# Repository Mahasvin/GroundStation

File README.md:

# GroundStation
Hardware of Ground Station for UTS Rocketry

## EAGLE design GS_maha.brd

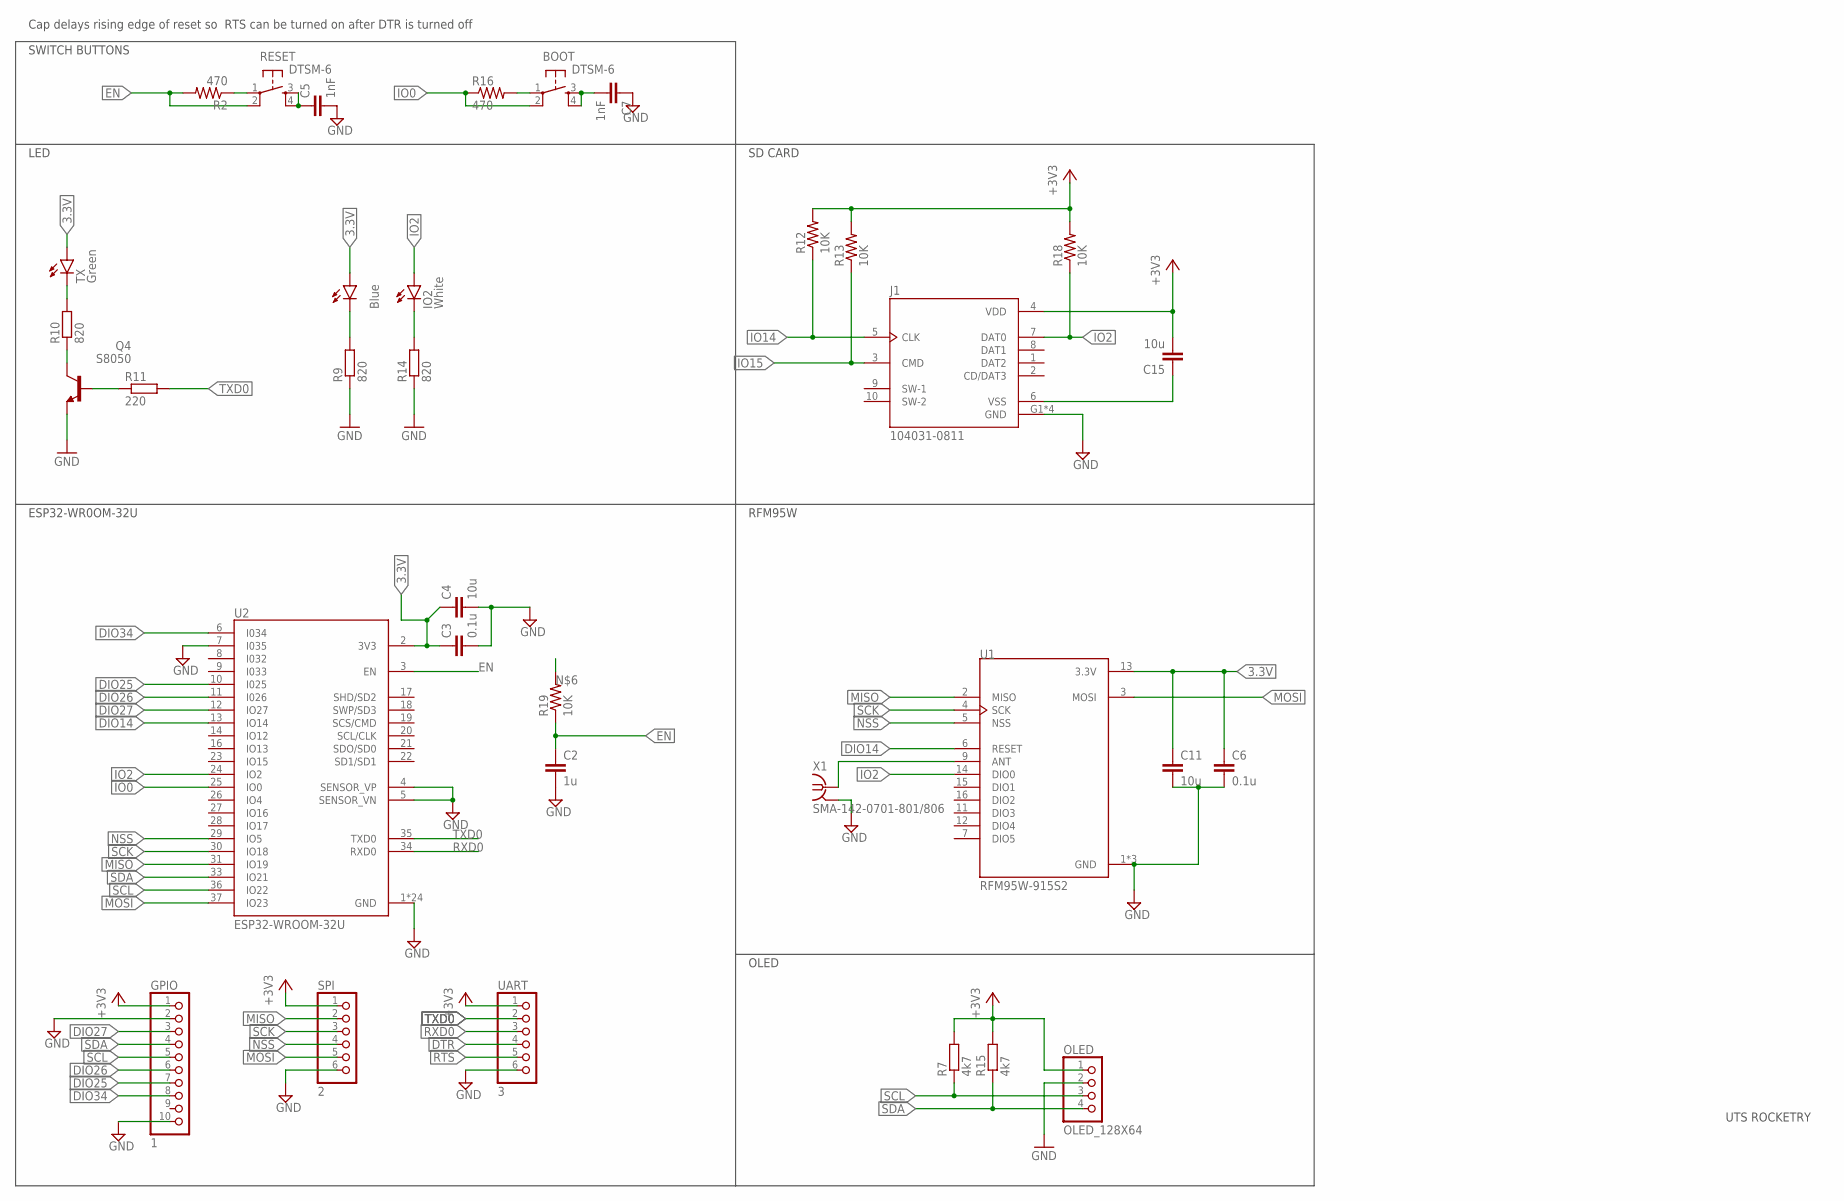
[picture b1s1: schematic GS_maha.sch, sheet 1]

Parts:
BOOT: DTSM-6
C2: 1u; C0805
C3, C6: 0.1u; C0805
C4, C11, C15: 10u; C0805
C5, C7: 1nF; C0805
GPIO: 1; 1X10
IO2: White; CHIP-LED0805
J1: 104031-0811; MOLEX_104031-0811
OLED: OLED_128X64
PWR: Blue; CHIP-LED0805
Q4: S8050; SOT95P237X110-3N
R2, R16: 470; R0805
R7, R15: 4k7; R0805
R9, R10, R14: 820; R0805
R11: 220; R0805
R12, R13, R18, R19: 10K; R0805
RESET: DTSM-6
SPI: 2; 1X06
TX: Green; CHIP-LED0805
U1: RFM95W-915S2; XCVR_RFM95W-915S2
U2: ESP32-WROOM-32U; XCVR_ESP32-WROOM-32U
UART: 3; 1X06
X1: SMA-142-0701-801/806; J502-ND-142-0701-801/806

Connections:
3.3V: C3.1, C4.1, C6.1, C11.1, PWR.A, TX.A, U1.13 (3.3V), U2.2 (3V3); also elsewhere on the board
+3V3: C15.2, GPIO.1, J1.4 (VDD), OLED.1, R7.2, R12.2, R13.2, R15.2, R18.2, SPI.1, UART.1
DIO14: U1.6 (RESET), U2.13 (IO14)
DIO25: GPIO.7, U2.10 (I025)
DIO26: GPIO.6, U2.11 (I026)
DIO27: GPIO.3, U2.12 (IO27)
DIO34: GPIO.8, U2.6 (I034)
DTR: UART.4; also elsewhere on the board
EN: C2.1, R2.2, R19.1, RESET.2, U2.3 (EN); also elsewhere on the board
GND: C2.2, C3.2, C4.2, C5.2, C6.2, C7.1, C11.2, GPIO.2, GPIO.10, J1.G1 (GND), J1.G2 (GND), J1.G3 (GND), J1.G4 (GND), OLED.2, Q4.2 (E), R9.1, R14.1, SPI.6, U1.1 (GND), U1.8 (GND), U1.10 (GND), U2.1 (GND), U2.4 (SENSOR_VP), U2.5 (SENSOR_VN), U2.7 (I035), U2.15 (GND), U2.38 (GND), U2.G.1 (GND), U2.G.2 (GND), U2.G.4 (GND), U2.G.5 (GND), U2.G.6 (GND), U2.G.7 (GND), U2.G.8 (GND), U2.G.9 (GND), U2.G.10 (GND), U2.G.11 (GND), U2.G.12 (GND), U2.G.13 (GND), U2.G.14 (GND), U2.G.15 (GND), U2.G.16 (GND), U2.G.17 (GND), U2.G.18 (GND), U2.G.19 (GND), U2.G.20 (GND), U2.G.21 (GND), U2.G.22 (GND), UART.6, X1.G@1 (2), X1.G@2 (2), X1.G@3 (2), X1.G@4 (2); also elsewhere on the board
IO0: BOOT.2, R16.1, U2.25 (IO0); also elsewhere on the board
IO2: IO2.A, J1.7 (DAT0), R18.1, U1.14 (DIO0), U2.24 (IO2)
IO14: J1.5 (CLK), R12.1
IO15: J1.3 (CMD), R13.1
MISO: SPI.2, U1.2 (MISO), U2.31 (IO19)
MOSI: SPI.5, U1.3 (MOSI), U2.37 (IO23)
unnamed: C15.1, J1.6 (VSS)
unnamed: U1.9 (ANT), X1.1
unnamed: R2.1, RESET.1
unnamed: BOOT.3, BOOT.4, C7.2
unnamed: PWR.C, R9.2
unnamed: IO2.C, R14.2
unnamed: C5.1, RESET.3, RESET.4
unnamed: BOOT.1, R16.2
unnamed: Q4.3 (C), R10.1
unnamed: Q4.1 (B), R11.1
unnamed: R10.2, TX.C
NSS: SPI.4, U1.5 (NSS), U2.29 (IO5)
RTS: UART.5; also elsewhere on the board
RXD0: U2.34 (RXD0), UART.3; also elsewhere on the board
SCK: SPI.3, U1.4 (SCK), U2.30 (IO18)
SCL: GPIO.5, OLED.3, R7.1, U2.36 (IO22)
SDA: GPIO.4, OLED.4, R15.1, U2.33 (IO21)
TXD0: R11.2, U2.35 (TXD0), UART.2; also elsewhere on the board

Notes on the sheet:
ESP32-WR0OM-32U
SWITCH BUTTONS
UTS ROCKETRY
RFM95W
LED
Cap delays rising edge of reset so RTS can be turned on after DTR is turned off
OLED
SD CARD

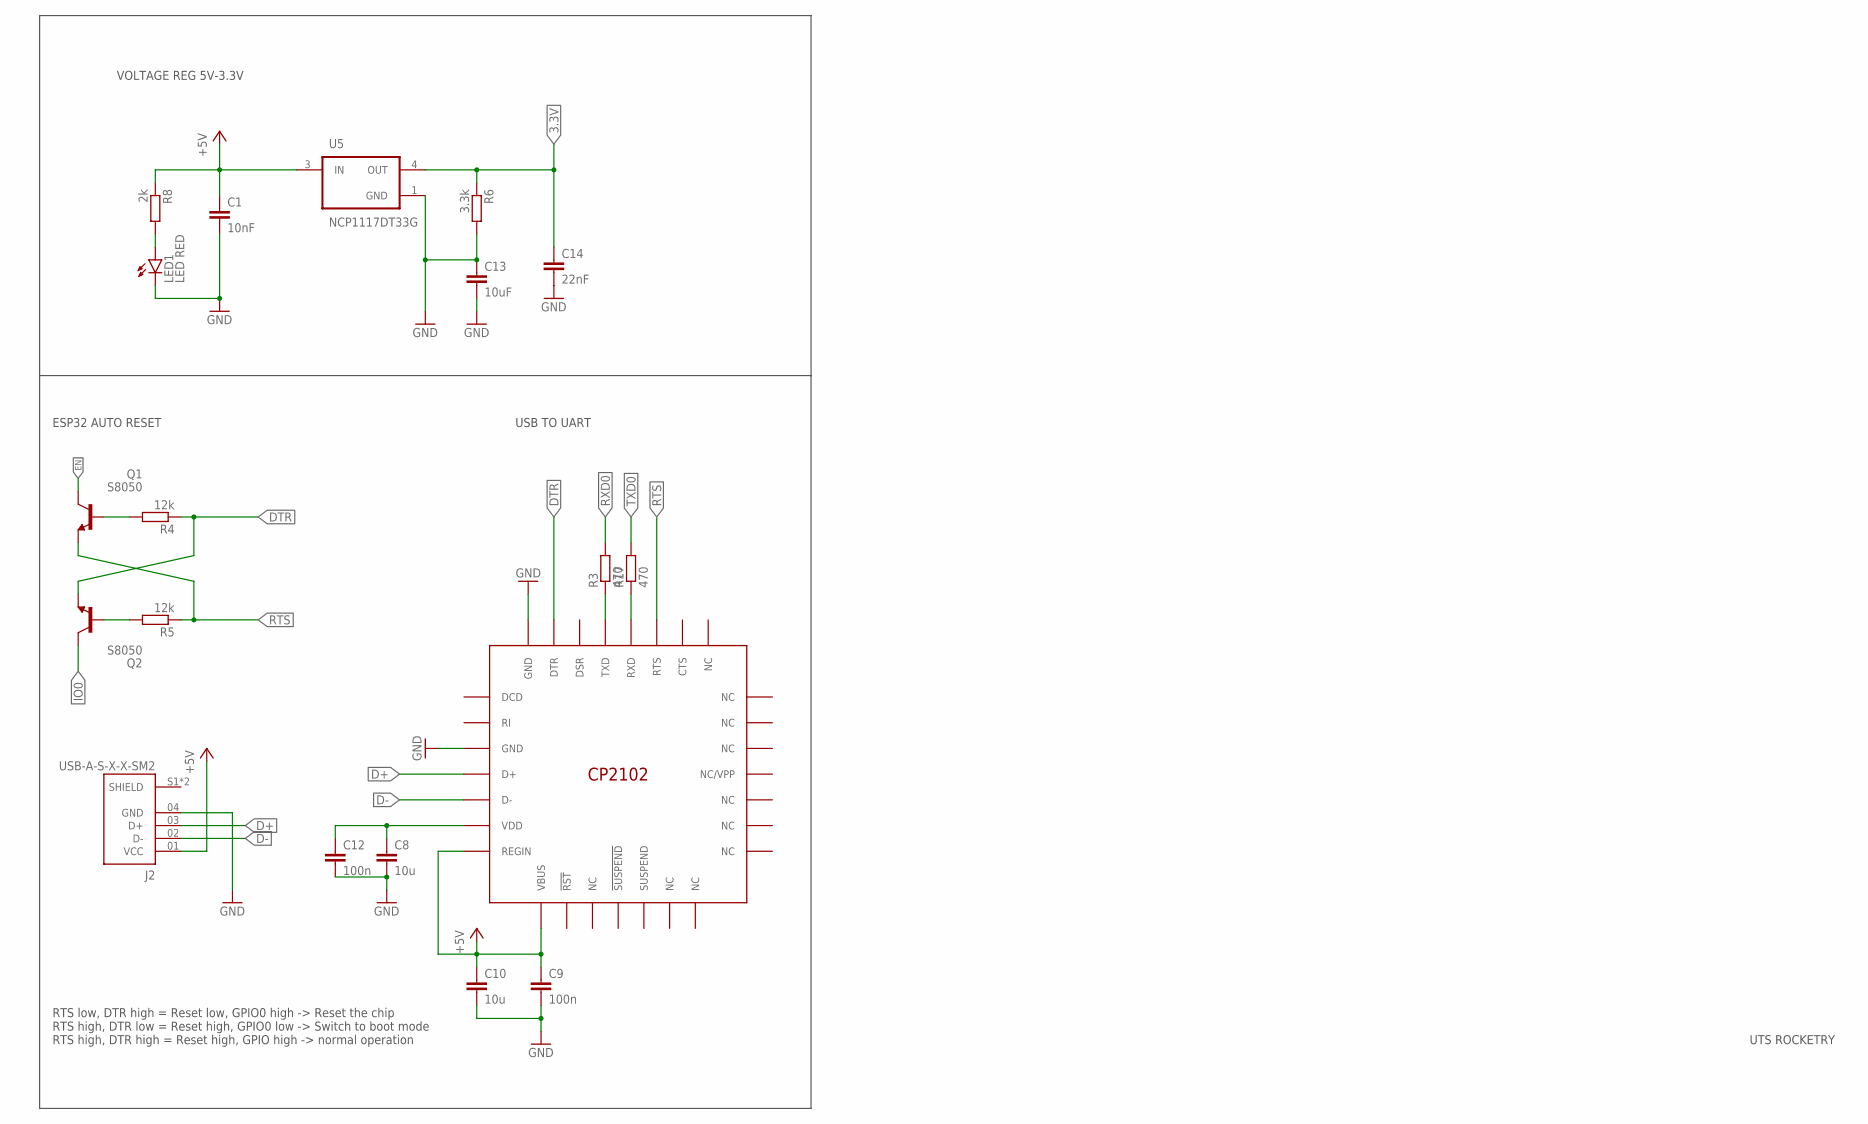
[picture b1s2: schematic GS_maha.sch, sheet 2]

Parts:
C1: 10nF; C0805
C8, C10: 10u; C0805
C9, C12: 100n; C0805
C13: 10uF; C0805
C14: 22nF; C0805
J2: USB-A-S-X-X-SM2; SAMTEC_USB-A-S-X-X-SM2
LED1: LED RED; CHIPLED_0805
Q1, Q2: S8050; SOT95P237X110-3N
R3, R17: 470; R0805
R4, R5: 12k; R0805
R6: 3.3k; R0805
R8: 2k; R0805
U3: CP2102; QFN50P500X500X100-29T300N
U5: NCP1117DT33G; VREG_NCP1117DT33G

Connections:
3.3V: C14.1, R6.1, U5.4 (OUT); also elsewhere on the board
+5V: C1.1, C9.1, C10.1, J2.01 (VCC), R8.1, U3.7 (REGIN), U3.8 (VBUS), U5.3 (IN)
D+: J2.03 (D+), U3.4 (D+)
D-: J2.02 (D-), U3.5 (D-)
DTR: Q2.2 (E), R4.1, U3.28 (DTR); also elsewhere on the board
EN: Q1.3 (C); also elsewhere on the board
GND: C1.2, C8.2, C9.2, C10.2, C12.2, C13.1, C13.2, C14.2, J2.04 (GND), LED1.C, R6.2, U3.3 (GND), U3.29 (GND), U5.1 (GND); also elsewhere on the board
IO0: Q2.3 (C); also elsewhere on the board
unnamed: R17.1, U3.25 (RXD)
unnamed: R3.1, U3.26 (TXD)
unnamed: Q1.1 (B), R4.2
unnamed: Q2.1 (B), R5.2
unnamed: C8.1, C12.1, U3.6 (VDD)
unnamed: LED1.A, R8.2
RTS: Q1.2 (E), R5.1, U3.24 (RTS); also elsewhere on the board
RXD0: R3.2; also elsewhere on the board
TXD0: R17.2; also elsewhere on the board

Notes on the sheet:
USB TO UART
ESP32 AUTO RESET
UTS ROCKETRY
RTS low, DTR high = Reset low, GPIO0 high -> Reset the chip RTS high, DTR low = Reset high, GPIO0 low -> Switch to boot mode RTS high, DTR high = Reset high, GPIO high -> normal operation
VOLTAGE REG 5V-3.3V

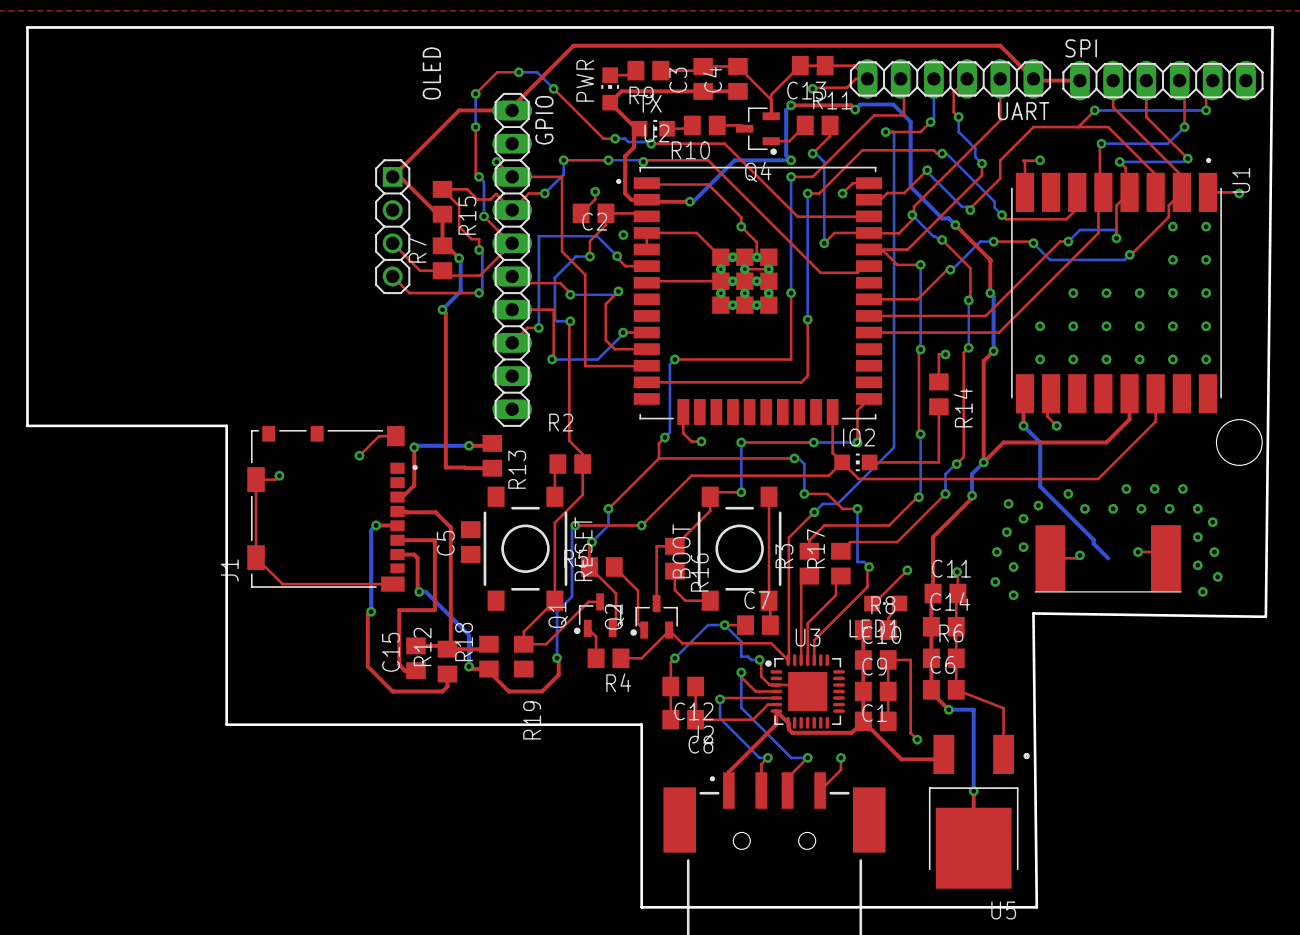
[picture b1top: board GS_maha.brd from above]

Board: 2 copper layers, 95.2 x 67.3 mm, 53 parts (1 on the bottom side), 43 nets.

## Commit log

2022-01-25 Hardware Schematics Eagle
